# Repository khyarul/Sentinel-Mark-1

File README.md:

# SENTINEL MARK I (PSIONIC) - Line Follower Path Planning + Oled I2C User Interface
Feature:
  - Microcontroller used: STM32F103CBT6 (Breakout board: Maple Mini, 128KB Flash, 20KB SRAM)
  - Bootloader: maple bootloader v2
  - EEPROM: external EEPROM (256Kb/32KB)
  - Motor Encoder (using interrupt) and Timer mode
  - Oled I2C LCD 128x64
  - multiplexed sensor using CD4051
  - UI Path Planning Configuration Menu

Library Arduino yang diperlukan:
1. **extEEPROM**: https://github.com/JChristensen/extEEPROM
2. **SSD1306 (I2C OLED)**: https://github.com/olikraus/u8g2

# SUPPORT & DONATE this Open-Source project: 
  - PAYPAL  : [SentinelCreative](https://www.paypal.me/sentinelcreative "PAYPAL")
  - BNI     : 0718053662 (Khyarul Arham)
  - Mandiri : 1130012279398 (Khyarul Arham)

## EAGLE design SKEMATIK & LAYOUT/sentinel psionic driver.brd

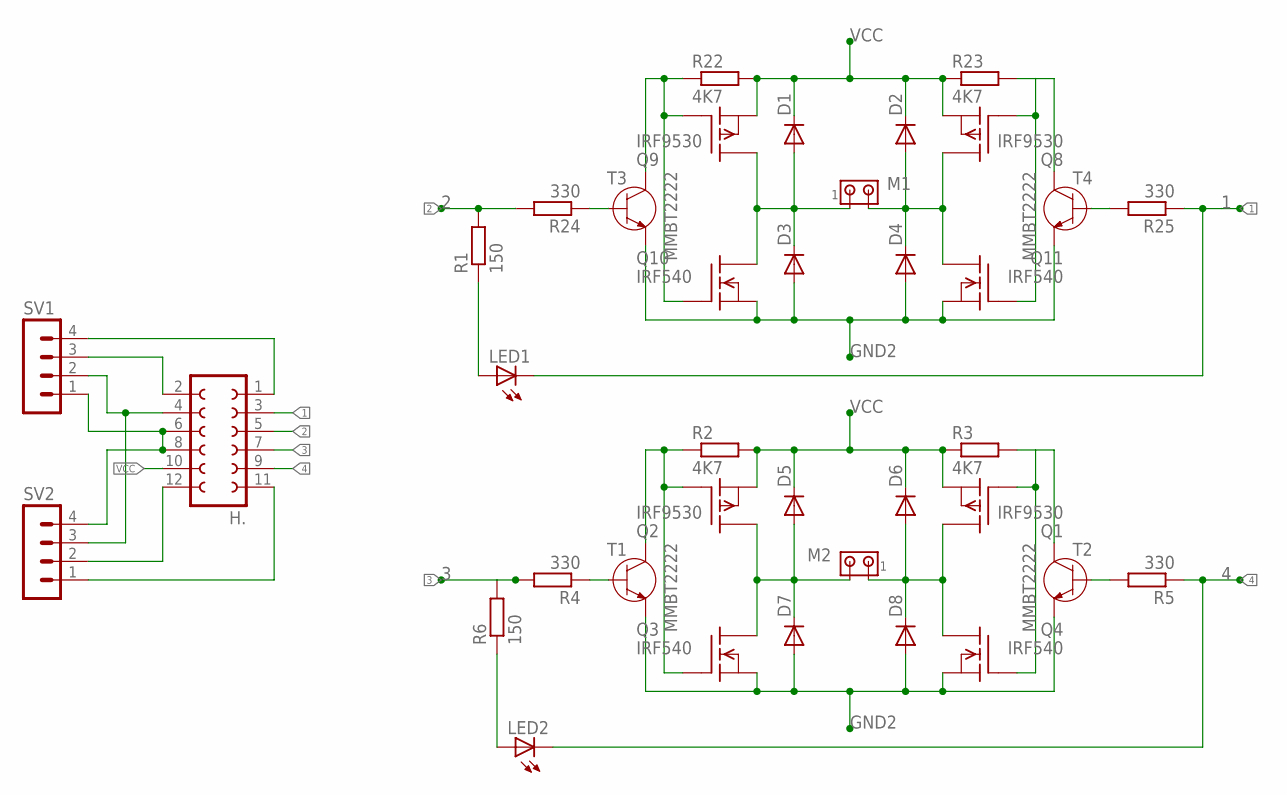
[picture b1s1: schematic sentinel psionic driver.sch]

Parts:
D1, D2, D3, D4, D5, D6, D7, D8: DIODE-DO-214AC; DO-214AC
H.: FE06-2
LED1, LED2: LED3MM
M1, M2: MTA02-100; 10X02MTA
Q1, Q2, Q8, Q9: IRF9530; TO220
Q3, Q4, Q10, Q11: IRF540; TO220
R1, R6: 150; R1206
R2, R3, R22, R23: 4K7; R1206
R4, R5, R24, R25: 330; R1206
SV1, SV2: MA04-1
T1, T2, T3, T4: MMBT2222; SOT23

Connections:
1: H..3, LED1.K (C), R25.1
2: H..5, R1.2, R24.2
3: H..7, R4.2, R6.2
4: H..9, LED2.K (C), R5.1
GND2: D3.A, D4.A, D7.A, D8.A, H..6, H..8, Q3.3 (S), Q4.3 (S), Q10.3 (S), Q11.3 (S), SV1.1, SV2.4, T1.2 (E), T2.2 (E), T3.2 (E), T4.2 (E)
unnamed: R25.2, T4.1 (B)
unnamed: LED1.A, R1.1
unnamed: R5.2, T2.1 (B)
unnamed: Q2.1 (G), Q3.1 (G), R2.1, T1.3 (C)
unnamed: D5.A, D7.C, M2.2, Q2.2 (D), Q3.2 (D)
unnamed: D6.A, D8.C, M2.1, Q1.2 (D), Q4.2 (D)
unnamed: Q1.1 (G), Q4.1 (G), R3.2, T2.3 (C)
unnamed: Q9.1 (G), Q10.1 (G), R22.1, T3.3 (C)
unnamed: R4.1, T1.1 (B)
unnamed: LED2.A, R6.1
unnamed: H..4, SV1.2, SV2.3
unnamed: H..2, SV1.3
unnamed: H..1, SV1.4
unnamed: H..12, SV2.2
unnamed: H..11, SV2.1
unnamed: D1.A, D3.C, M1.1, Q9.2 (D), Q10.2 (D)
unnamed: D2.A, D4.C, M1.2, Q8.2 (D), Q11.2 (D)
unnamed: Q8.1 (G), Q11.1 (G), R23.2, T4.3 (C)
unnamed: R24.1, T3.1 (B)
VCC: D1.C, D2.C, D5.C, D6.C, H..10, Q1.3 (S), Q2.3 (S), Q8.3 (S), Q9.3 (S), R2.2, R3.1, R22.2, R23.1

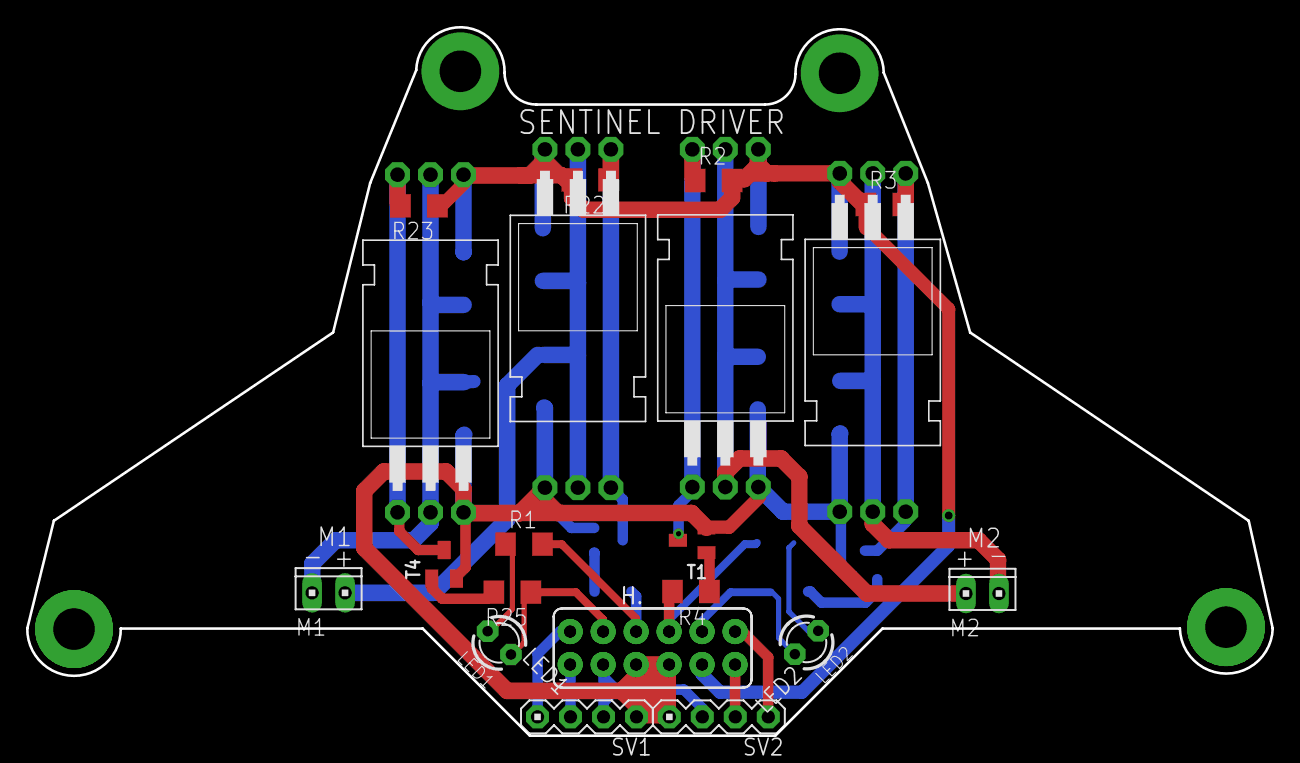
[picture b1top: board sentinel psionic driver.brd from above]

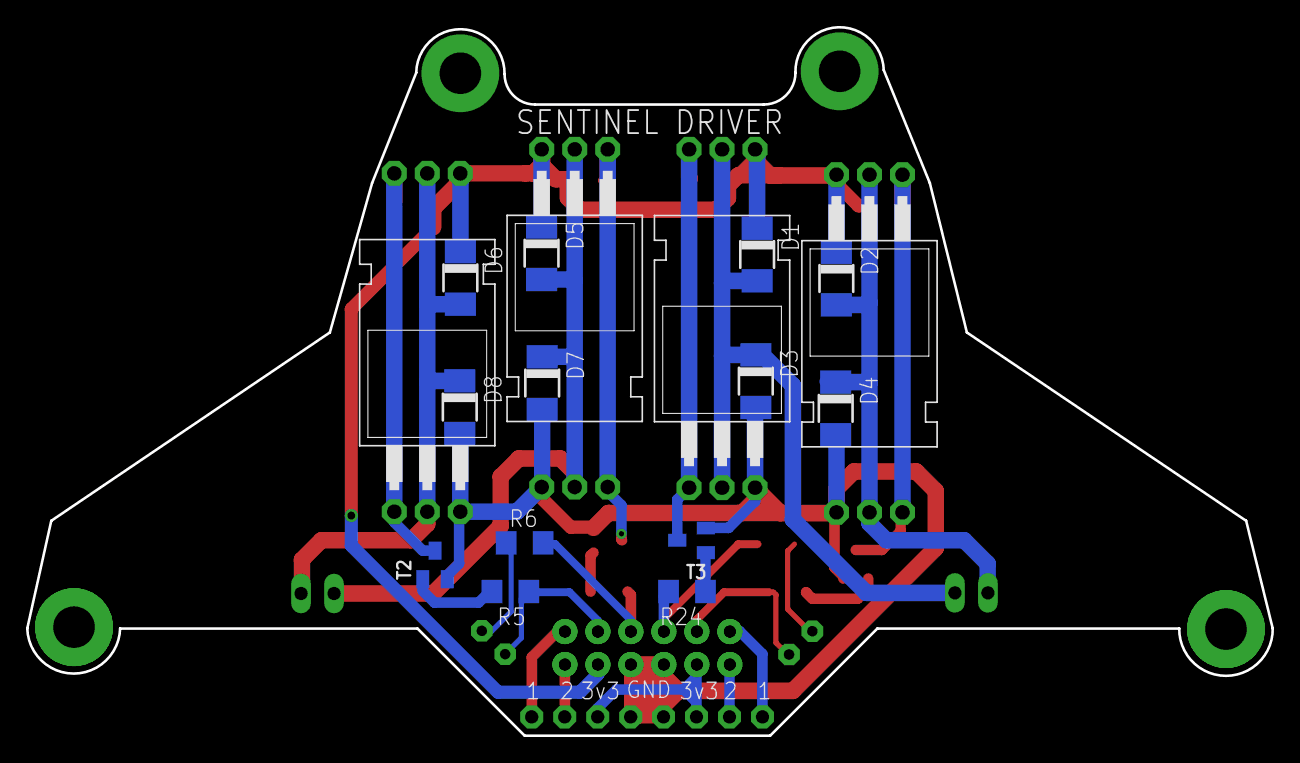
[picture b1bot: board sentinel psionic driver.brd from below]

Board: 2 copper layers, 95.9 x 54.5 mm, 38 parts (17 on the bottom side), 25 nets.

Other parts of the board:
H: FE06-2

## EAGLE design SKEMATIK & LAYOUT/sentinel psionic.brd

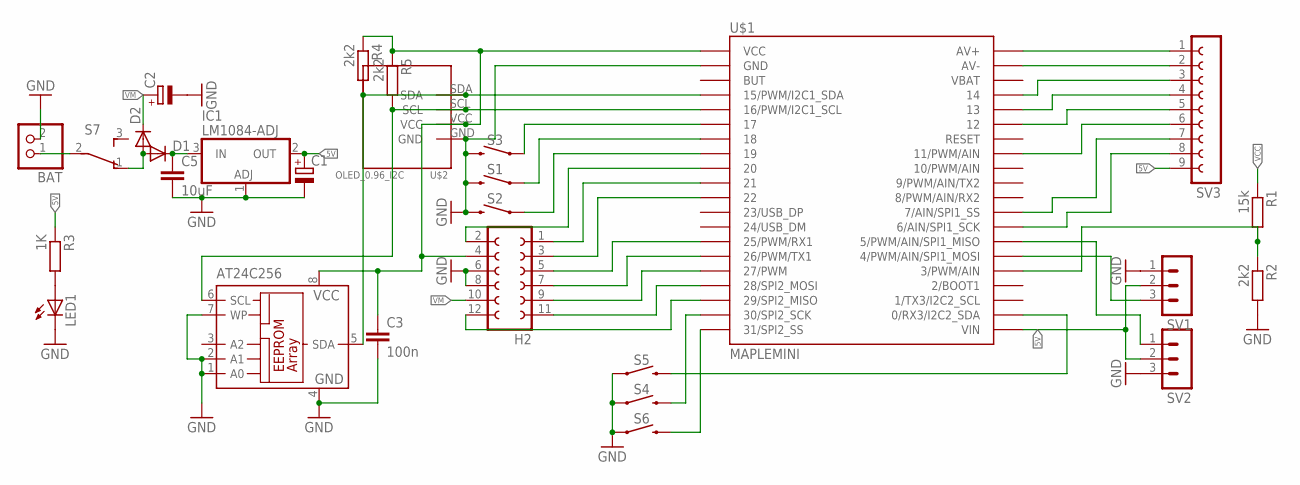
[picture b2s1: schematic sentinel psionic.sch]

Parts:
AT24C256: 24AA01SN; SO-08
BAT: PINHD-1X2; 1X02
C1, C2: CPOL-EU153CLV-0605; 153CLV-0605
C3: 100n; C1206
C5: 10uF; C1206
D1, D2: DIODE-DO-214AC; DO-214AC
H2: FE06-2
IC1: LM1084-ADJ; TO263-3
LED1: LED_E; LED_1206
R1: 15k; R1206
R2, R4, R5: 2k2; R1206
R3: 1K; R1206
S1, S2, S3, S4, S5, S6: MOMENTARY-SWITCH-SPST-SMD-6.0X3.5MM; TACTILE_SWITCH_SMD_6.0X3.5MM
S7: TL36PO; TL3XPO
SV1, SV2: MA03-1
SV3: FE09-1; FE09
U$1: MAPLEMINI; 20-DIP
U$2: OLED_0.96_I2C

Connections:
5V: C1.+, IC1.2 (OUT), R3.1, SV1.2, SV2.2, SV3.9, U$1.21 (VIN)
5V1: AT24C256.8 (VCC), C3.1, H2.4, R4.1, R5.1, U$1.1 (VCC), U$2.VCC
+: BAT.1, S7.2
GND: AT24C256.1 (A0), AT24C256.2 (A1), AT24C256.4 (GND), AT24C256.7 (WP), BAT.2, C1.-, C2.-, C3.2, C5.2, H2.6, H2.8, IC1.1 (ADJ), LED1.C, R2.2, S1.2, S2.2, S3.2, S4.1, S5.1, S6.1, SV1.1, SV2.3, U$1.2 (GND), U$2.GND
unnamed: R1.2, R2.1, U$1.25 (3/PWM/AIN)
unnamed: AT24C256.5 (SDA), R4.2, U$1.4 (15/PWM/I2C1_SDA), U$2.SDA
unnamed: LED1.A, R3.2
unnamed: SV3.8, U$1.28 (6/AIN/SPI1_SCK)
unnamed: SV3.1, U$1.40 (AV+)
unnamed: SV3.2, U$1.39 (AV-)
unnamed: SV3.3, U$1.37 (14)
unnamed: SV3.4, U$1.36 (13)
unnamed: SV3.5, U$1.35 (12)
unnamed: SV3.6, U$1.33 (11/PWM/AIN)
unnamed: SV3.7, U$1.29 (7/AIN/SPI1_SS)
unnamed: S3.1, U$1.6 (17)
unnamed: S1.1, U$1.7 (18)
unnamed: S2.1, U$1.8 (19)
unnamed: S6.2, U$1.20 (31/SPI2_SS)
unnamed: S4.2, U$1.19 (30/SPI2_SCK)
unnamed: S5.2, U$1.22 (0/RX3/I2C2_SDA)
unnamed: C5.1, D1.C, IC1.3 (IN)
unnamed: H2.2, U$1.9 (20)
unnamed: SV2.1, U$1.27 (5/PWM/AIN/SPI1_MISO)
unnamed: SV1.3, U$1.26 (4/PWM/AIN/SPI1_MOSI)
unnamed: H2.1, U$1.10 (21)
unnamed: H2.11, U$1.17 (28/SPI2_MOSI)
unnamed: H2.12, U$1.18 (29/SPI2_MISO)
unnamed: H2.3, U$1.11 (22)
unnamed: H2.5, U$1.14 (25/PWM/RX1)
unnamed: H2.7, U$1.15 (26/PWM/TX1)
unnamed: H2.9, U$1.16 (27/PWM)
unnamed: AT24C256.6 (SCL), R5.2, U$1.5 (16/PWM/I2C1_SCL), U$2.SCL
VCC: D1.A, D2.A, R1.1, S7.1 (O)
VM: C2.+, D2.C, H2.10

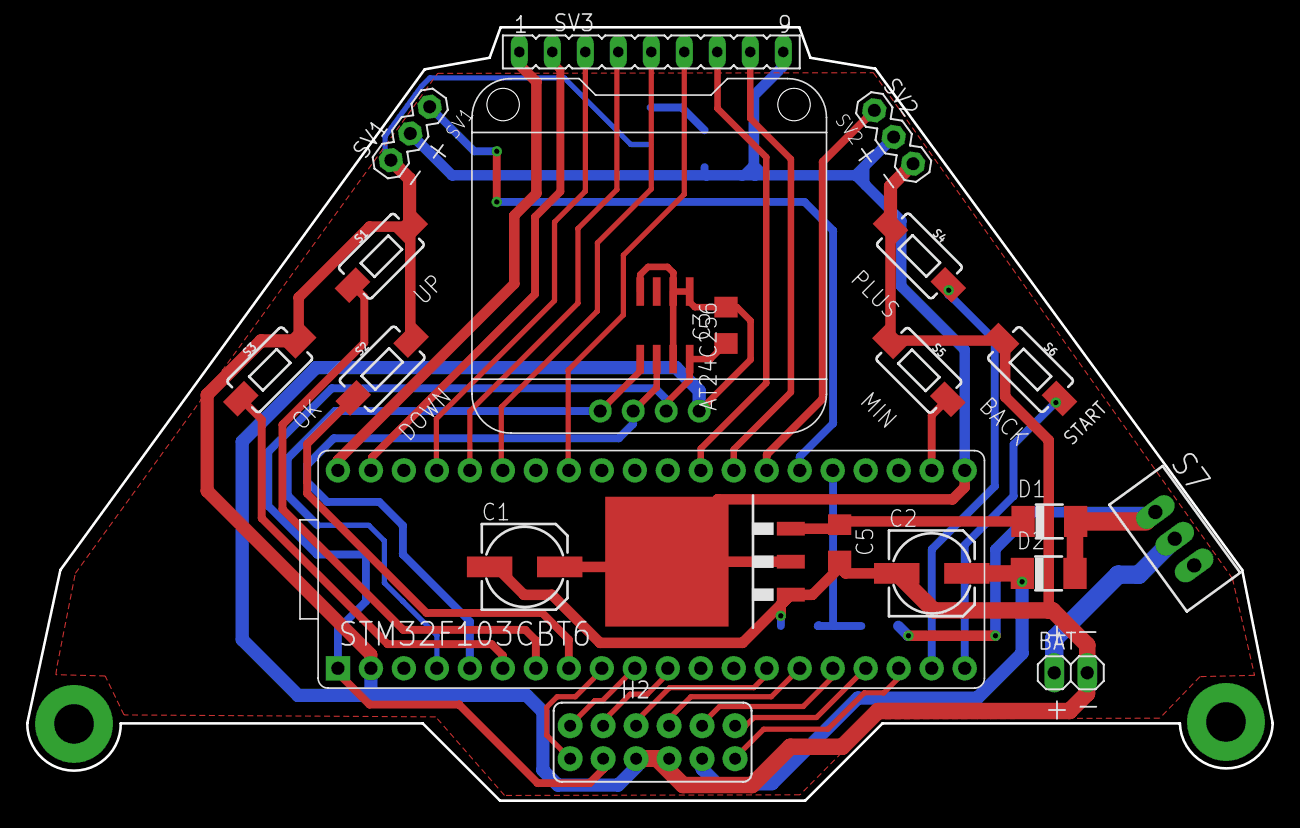
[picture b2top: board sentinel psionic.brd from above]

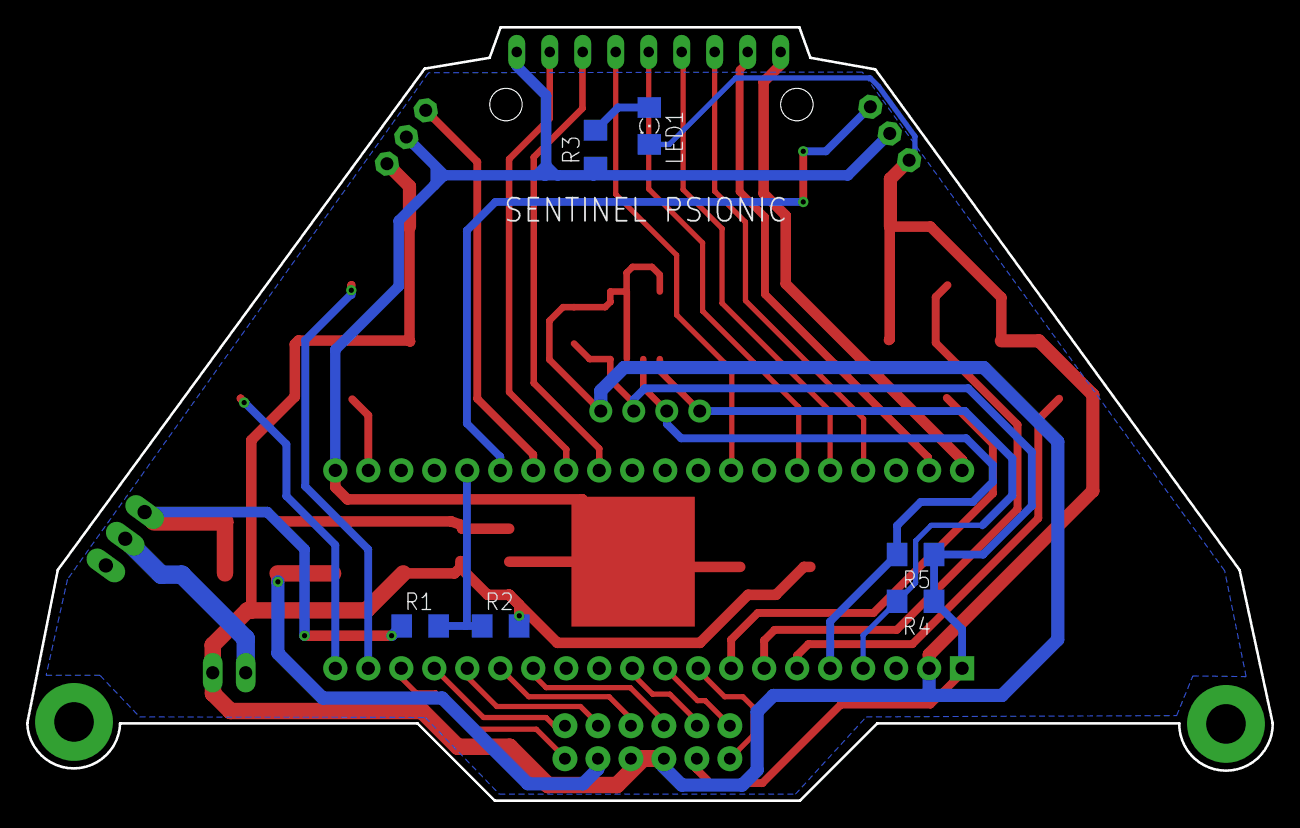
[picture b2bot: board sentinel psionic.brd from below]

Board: 2 copper layers, 95.9 x 59.6 mm, 28 parts (6 on the bottom side), 35 nets.

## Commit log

2020-03-29 Create Code
2020-10-01 skematik sensor (Eagle)

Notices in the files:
parts and their libraries:
button: Licensing: Creative Commons ShareAlike 4.0 International - https://creativecommons.org/licenses/by-sa/4.0
